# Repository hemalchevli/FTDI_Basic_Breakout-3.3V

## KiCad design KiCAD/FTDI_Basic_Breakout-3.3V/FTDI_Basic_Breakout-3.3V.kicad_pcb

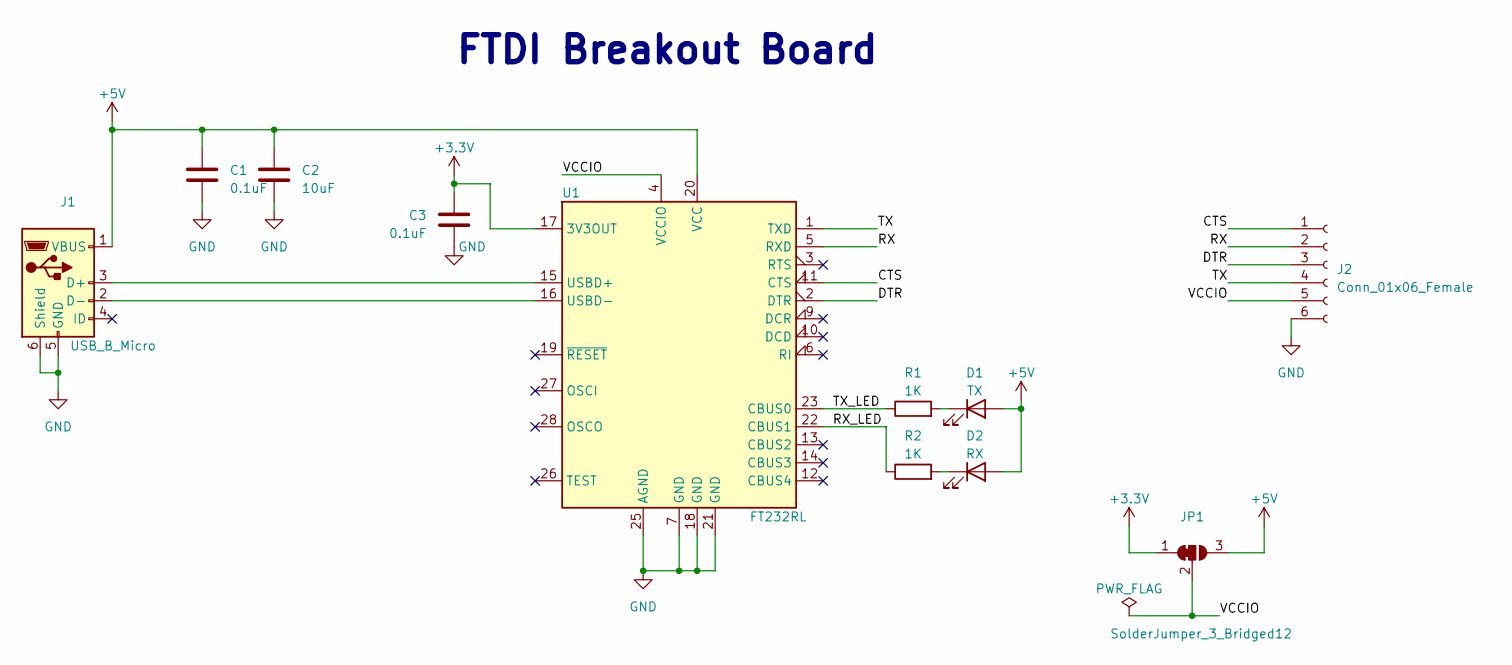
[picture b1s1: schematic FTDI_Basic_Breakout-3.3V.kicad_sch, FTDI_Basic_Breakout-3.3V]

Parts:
C1, C3: 0.1uF; C_0603_1608Metric
C2: 10uF; C_0805_2012Metric
D1: TX; LED_0603_1608Metric
D2: RX; LED_0603_1608Metric
J1: USB_B_Micro; USB_Micro-B_Wuerth_629105150521
J2: Conn_01x06_Female; PinHeader_1x06_P2.54mm_Vertical
JP1: SolderJumper_3_Bridged12; SolderJumper-3_P1.3mm_Bridged12_RoundedPad1.0x1.5mm
R1, R2: 1K; R_0603_1608Metric
U1: FT232RL; SSOP-28_5.3x10.2mm_P0.65mm

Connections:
+3V3: C3.2, JP1.1 (A), U1.17 (3V3OUT)
+5V: C1.1, C2.1, D1.2 (A), D2.2 (A), J1.1 (VBUS), JP1.3 (B), U1.20 (VCC)
/CTS: J2.1, U1.11 (CTS)
/DTR: J2.3, U1.2 (DTR)
/RX: J2.2, U1.5 (RXD)
/RX_LED: R2.1, U1.22 (CBUS1)
/TX: J2.4, U1.1 (TXD)
/TX_LED: R1.1, U1.23 (CBUS0)
/VCCIO: J2.5, JP1.2 (C), U1.4 (VCCIO)
GND: C1.2, C2.2, C3.1, J1.5 (GND), J1.6 (Shield), J2.6, U1.7 (GND), U1.18 (GND), U1.21 (GND), U1.25 (AGND)
unnamed: D1.1 (K), R1.2
unnamed: D2.1 (K), R2.2
unnamed: J1.2 (D-), U1.16 (USBD-)
unnamed: J1.3 (D+), U1.15 (USBD+)

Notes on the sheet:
FTDI Breakout Board

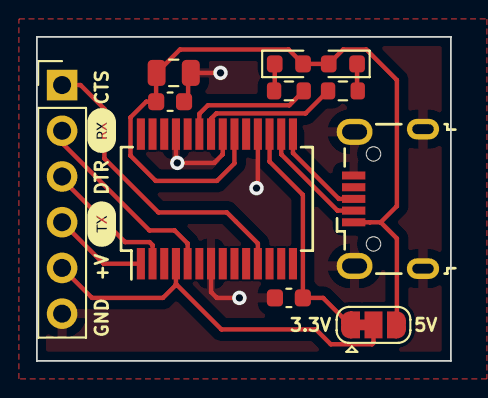
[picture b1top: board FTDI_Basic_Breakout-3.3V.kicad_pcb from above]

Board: 2 copper layers, 23.0 x 18.0 mm, 13 parts (0 on the bottom side), 14 nets.

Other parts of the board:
svg2mod, svg2mod#2: G***; svg2mod

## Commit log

2021-06-28 Adds KiCAD files
